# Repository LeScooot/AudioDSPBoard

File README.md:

## Members
Ryan Jeronimus, EE Student (Graduating 2027)

ryanjeronimus@vt.edu

## Mentor
MENTOR NAME HERE

## Current Status
IN PROGRESS

## Project Overview

PCB featuring 3.5mm audio inputs and outputs, an audio CODEC for high-quality audio sampling and reconstruction, bare-metal STM32 board for implementing DSP algorithms, and a small i2c LED display for displaying information pertaining to the audio effects implemented on the STM32 (real-time display). Features programmable potentiometers and buttons for use in DSP implementations. Battery powered for ease of use when travelling. The system is intended as a portable, real-time audio effects processor for general listening applications.

## Educational Value Added
This project teaches about PCB design, power electronics, bare-metal C programming practices, and DSP for audio applications (which includes topics widely applicable to general DSP). Audio-specific communication protocols such as i2s would also be taught with the completion of this project.
## Tasks

<!-- Your Text Here. You may work with your mentor on this later when they are assigned -->

## Design Decisions

<!-- Your Text Here. You may work with your mentor on this later when they are assigned -->

## Design Misc

<!-- Your Text Here. You may work with your mentor on this later when they are assigned -->

## Steps for Documenting Your Design Process

<!-- Your Text Here. You may work with your mentor on this later when they are assigned -->

## BOM + Component Cost

<!-- Your Text Here. You may work with your mentor on this later when they are assigned -->

## Timeline

<!-- Your Text Here. You may work with your mentor on this later when they are assigned -->

## Useful Links

<!-- Your Text Here. You may work with your mentor on this later when they are assigned -->

## Log

<!-- Your Text Here. You may work with your mentor on this later when they are assigned -->

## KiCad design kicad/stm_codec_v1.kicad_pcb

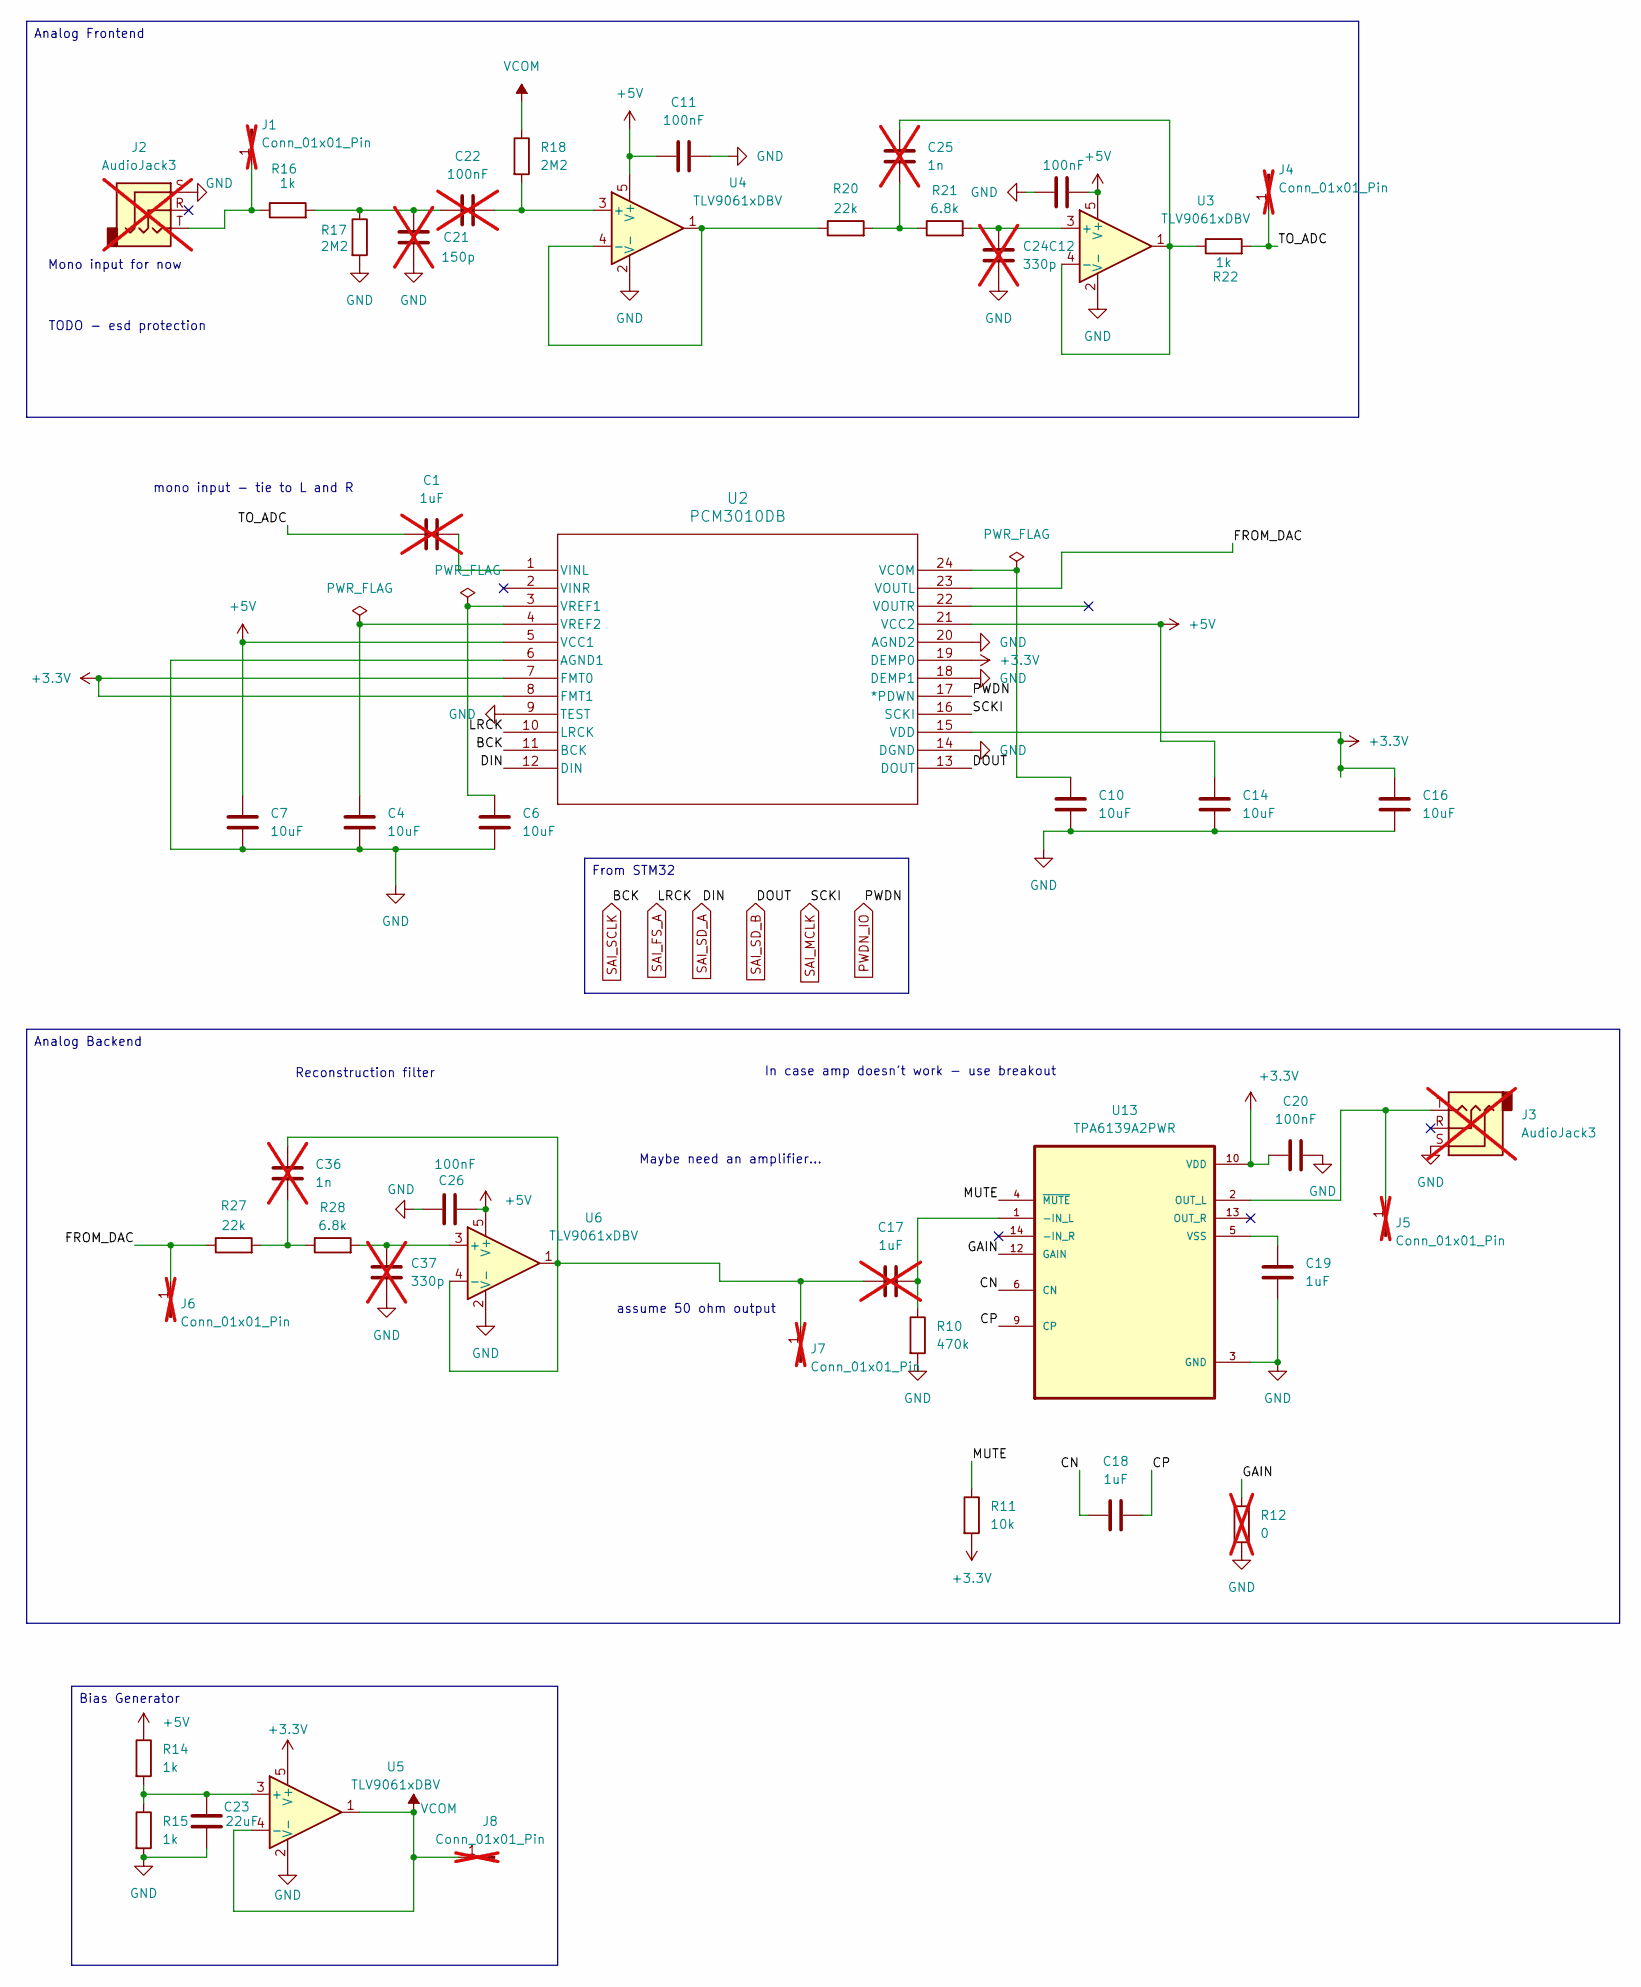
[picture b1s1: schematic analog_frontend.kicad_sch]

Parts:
C1, C17: 1uF; C_Rect_L16.5mm_W4.9mm_P15.00mm_MKT; not fitted
C4, C7: 10uF; C_0805_2012Metric_Pad1.18x1.45mm_HandSolder; LCSC Part # C15850
C6, C10, C14, C16: 10uF; C_1206_3216Metric_Pad1.33x1.80mm_HandSolder; LCSC Part # C13585
C11, C12, C20, C26: 100nF; C_0805_2012Metric_Pad1.18x1.45mm_HandSolder; LCSC Part # C49678
C18, C19: 1uF; C_1206_3216Metric_Pad1.33x1.80mm_HandSolder; LCSC Part # C1848
C21: 150p; C_Rect_L7.0mm_W2.5mm_P5.00mm; not fitted
C22: 100nF; C_Rect_L9.0mm_W4.0mm_P7.50mm_MKT; not fitted
C23: 22uF; C_1206_3216Metric_Pad1.33x1.80mm_HandSolder; LCSC Part # C12891
C24: 330p; C_Rect_L9.0mm_W4.0mm_P7.50mm_MKT; not fitted
C25, C36: 1n; C_Rect_L7.0mm_W2.5mm_P5.00mm; not fitted
C37: 330p; C_Rect_L7.0mm_W2.5mm_P5.00mm; not fitted
J1, J4, J5, J6, J7, J8: Conn_01x01_Pin; PinHeader_1x01_P2.54mm_Vertical; not fitted
J2, J3: AudioJack3; Jack_3.5mm_CUI_SJ-3523-SMT_Horizontal; not fitted
R10: 470k; R_0805_2012Metric_Pad1.20x1.40mm_HandSolder; LCSC Part # C17709
R11: 10k; R_0805_2012Metric_Pad1.20x1.40mm_HandSolder; LCSC Part # C17414
R12: 0; R_0805_2012Metric_Pad1.20x1.40mm_HandSolder; not fitted
R14, R15, R16, R22: 1k; R_0805_2012Metric_Pad1.20x1.40mm_HandSolder; LCSC Part # C702831
R17, R18: 2M2; R_0805_2012Metric_Pad1.20x1.40mm_HandSolder; LCSC Part # C17513
R20, R27: 22k; R_0805_2012Metric_Pad1.20x1.40mm_HandSolder; LCSC Part # C702833
R21, R28: 6.8k; R_0805_2012Metric_Pad1.20x1.40mm_HandSolder; LCSC Part # C17772
U2: PCM3010DB; DB24; LCSC Part # C2873586
U3, U4, U5, U6: TLV9061xDBV; SOT-23-5; LCSC Part # C398358
U13: TPA6139A2PWR; SOP65P640X120-14N; LCSC Part # C2870791

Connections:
+3.3V: C16.1, C20.1, R11.2, U2.7 (FMT0), U2.8 (FMT1), U2.15 (VDD), U2.19 (DEMP0), U5.5 (V+), U13.10 (VDD); also elsewhere on the board
+5V: C7.1, C11.1, C12.1, C14.1, C26.1, R14.1, U2.5 (VCC1), U2.21 (VCC2), U3.5 (V+), U4.5 (V+), U6.5 (V+); also elsewhere on the board
/Analog Frontend/CN: C18.1, U13.6 (CN)
/Analog Frontend/CP: C18.2, U13.9 (CP)
/Analog Frontend/FROM_DAC: J6.1, R27.1, U2.23 (VOUTL)
/Analog Frontend/GAIN: R12.1, U13.12 (GAIN)
/Analog Frontend/MUTE: R11.1, U13.4 (~MUTE)
/Analog Frontend/TO_ADC: C1.2, J4.1, R22.2
GND: C4.2, C6.2, C7.2, C10.2, C11.2, C12.2, C14.2, C16.2, C19.2, C20.2, C21.2, C23.2, C24.2, C26.2, C37.2, J2.S, J3.S, R10.2, R12.2, R15.2, R17.2, U2.6 (AGND1), U2.9 (TEST), U2.14 (DGND), U2.18 (DEMP1), U2.20 (AGND2), U3.2 (V-), U4.2 (V-), U5.2 (V-), U6.2 (V-), U13.3 (GND), U13.11 (GND); also elsewhere on the board
unnamed: C21.1, C22.2, R16.2, R17.1
unnamed: C25.2, R20.2, R21.1
unnamed: C36.2, R27.2, R28.1
unnamed: J1.1, J2.T, R16.1
unnamed: J3.T, J5.1, U13.2 (OUT_L)
unnamed: C17.1, C36.1, J7.1, U6.1, U6.4 (-)
unnamed: C10.1, U2.24 (VCOM)
unnamed: C1.1, U2.1 (VINL)
unnamed: C6.1, U2.3 (VREF1)
unnamed: C4.1, U2.4 (VREF2)
unnamed: C24.1, R21.2, U3.3 (+)
unnamed: C25.1, R22.1, U3.1, U3.4 (-)
unnamed: C22.1, R18.2, U4.3 (+)
unnamed: R20.1, U4.1, U4.4 (-)
unnamed: C23.1, R14.2, R15.1, U5.3 (+)
unnamed: C37.1, R28.2, U6.3 (+)
unnamed: C17.2, R10.1, U13.1 (-IN_L)
unnamed: C19.1, U13.5 (VSS)
PWDN_IO: U2.17 (*PDWN); also elsewhere on the board
SAI_FS_A: U2.10 (LRCK); also elsewhere on the board
SAI_MCLK: U2.16 (SCKI); also elsewhere on the board
SAI_SCLK: U2.11 (BCK); also elsewhere on the board
SAI_SD_A: U2.12 (DIN); also elsewhere on the board
SAI_SD_B: U2.13 (DOUT); also elsewhere on the board
VCOM: J8.1, R18.1, U5.1, U5.4 (-)

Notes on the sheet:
In case amp doesn't work - use breakout
assume 50 ohm output
Reconstruction filter
Maybe need an amplifier...
Mono input for now
mono input - tie to L and R
TODO - esd protection
Analog Frontend
Bias Generator
Analog Backend
From STM32

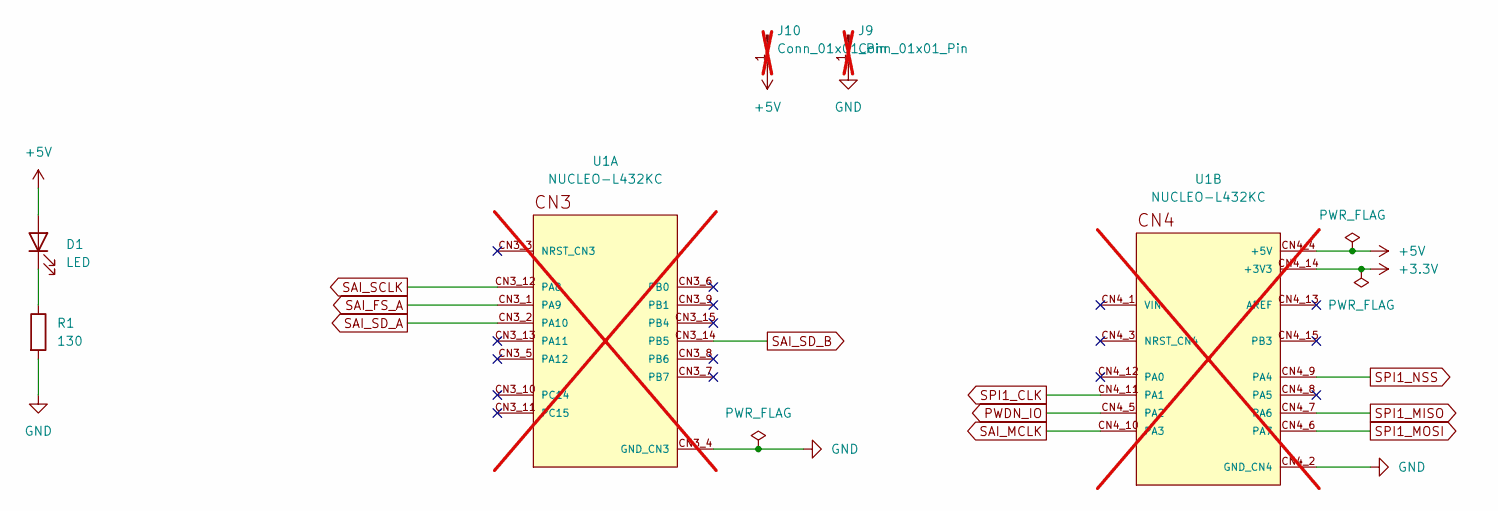
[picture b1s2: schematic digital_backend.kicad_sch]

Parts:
D1: LED; LED_0805_2012Metric_Pad1.15x1.40mm_HandSolder; LCSC Part # C2297
J9, J10: Conn_01x01_Pin; PinHeader_1x01_P2.54mm_Vertical; not fitted
R1: 130; R_0805_2012Metric_Pad1.20x1.40mm_HandSolder; LCSC Part # C178174
U1: NUCLEO-L432KC; MODULE_NUCLEO-L432KC; PARTREV N/A; not fitted

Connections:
+3.3V: U1.CN4_14 (+3V3); also elsewhere on the board
+5V: D1.2 (A), J10.1, U1.CN4_4 (+5V); also elsewhere on the board
GND: J9.1, R1.2, U1.CN3_4 (GND_CN3), U1.CN4_2 (GND_CN4); also elsewhere on the board
unnamed: D1.1 (K), R1.1
PWDN_IO: U1.CN4_5 (PA2); also elsewhere on the board
SAI_FS_A: U1.CN3_1 (PA9); also elsewhere on the board
SAI_MCLK: U1.CN4_10 (PA3); also elsewhere on the board
SAI_SCLK: U1.CN3_12 (PA8); also elsewhere on the board
SAI_SD_A: U1.CN3_2 (PA10); also elsewhere on the board
SAI_SD_B: U1.CN3_14 (PB5); also elsewhere on the board
SPI1_CLK: U1.CN4_11 (PA1)
SPI1_MISO: U1.CN4_7 (PA6)
SPI1_MOSI: U1.CN4_6 (PA7)
SPI1_NSS: U1.CN4_9 (PA4)

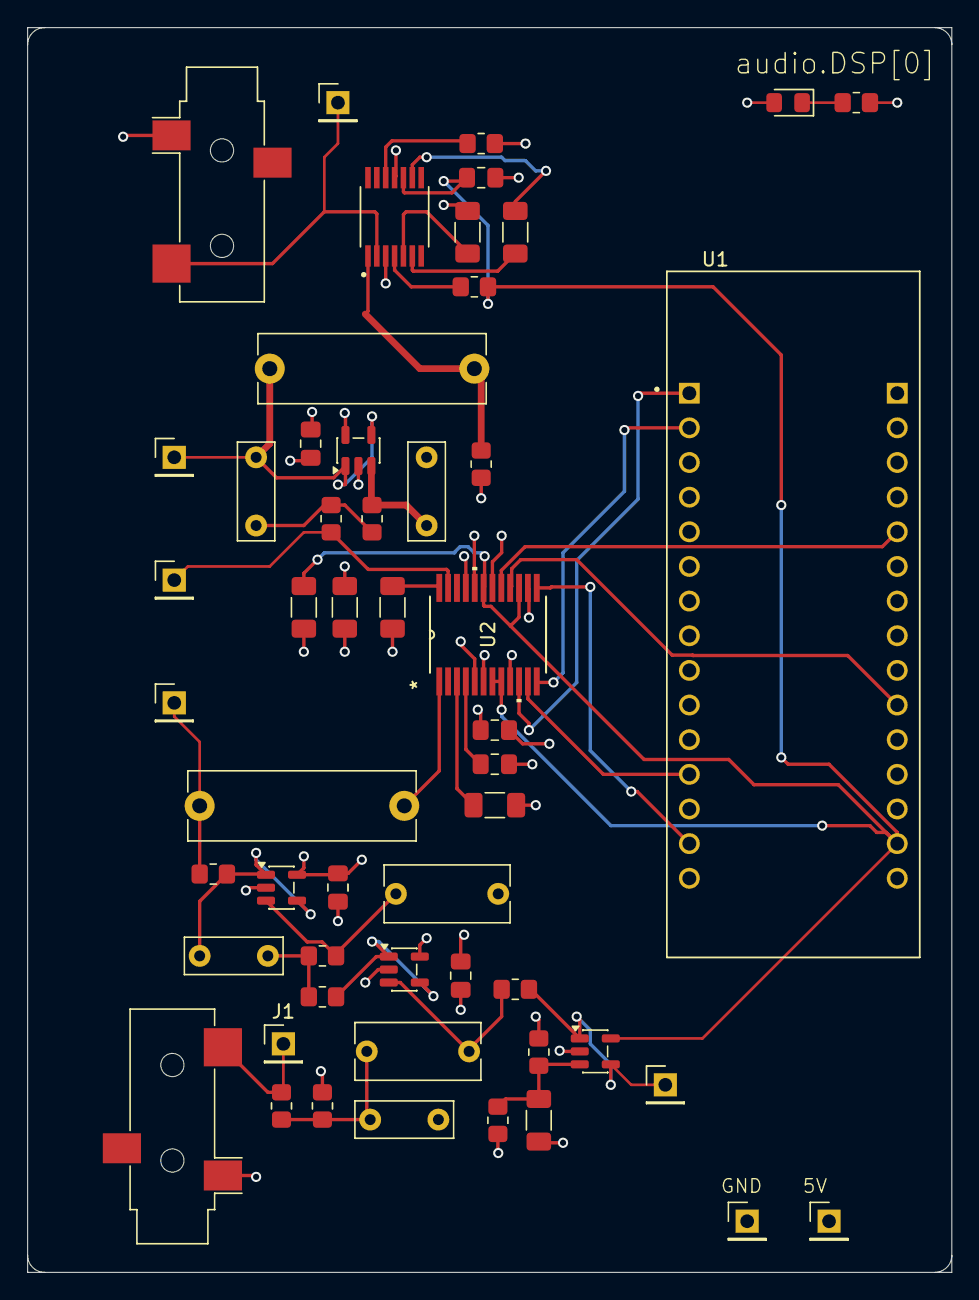
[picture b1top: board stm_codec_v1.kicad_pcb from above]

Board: 4 copper layers, 67.8 x 91.2 mm, 53 parts (0 on the bottom side), 35 nets.

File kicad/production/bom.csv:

Designator,Footprint,Quantity,Value,LCSC Part #
"C10, C14, C16, C6",1206,4,10uF,C13585
"C11, C12, C20, C26",0805,4,100nF,C49678
"C18, C19",1206,2,1uF,C1848
C23,1206,1,22uF,C12891
"C4, C7",0805,2,10uF,C15850
D1,0805,1,LED,C2297
R1,0805,1,130,C178174
R10,0805,1,470k,C17709
R11,0805,1,10k,C17414
"R14, R15, R16, R22",0805,4,1k,C702831
"R17, R18",0805,2,2M2,C17513
"R20, R27",0805,2,22k,C702833
"R21, R28",0805,2,6.8k,C17772
U13,SOP65P640X120-14N,1,TPA6139A2PWR,C2870791
U2,DB24,1,PCM3010DB,C2873586
"U3, U4, U5, U6",SOT-23-5,4,TLV9061xDBV,C398358

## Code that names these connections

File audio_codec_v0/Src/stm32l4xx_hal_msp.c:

/* USER CODE BEGIN Header */
/**
  ******************************************************************************
  * @file         stm32l4xx_hal_msp.c
  * @brief        This file provides code for the MSP Initialization
  *               and de-Initialization codes.
  ******************************************************************************
  * @attention
  *
  * Copyright (c) 2026 STMicroelectronics.
  * All rights reserved.
  *
  * This software is licensed under terms that can be found in the LICENSE file
  * in the root directory of this software component.
  * If no LICENSE file comes with this software, it is provided AS-IS.
  *
  ******************************************************************************
  */
/* USER CODE END Header */
/* Includes ------------------------------------------------------------------*/
#include "main.h"
/* USER CODE BEGIN Includes */

/* USER CODE END Includes */

/* Private typedef -----------------------------------------------------------*/
/* USER CODE BEGIN TD */

/* USER CODE END TD */

/* Private define ------------------------------------------------------------*/
/* USER CODE BEGIN Define */

/* USER CODE END Define */

/* Private macro -------------------------------------------------------------*/
/* USER CODE BEGIN Macro */

/* USER CODE END Macro */

/* Private variables ---------------------------------------------------------*/
/* USER CODE BEGIN PV */

/* USER CODE END PV */

/* Private function prototypes -----------------------------------------------*/
/* USER CODE BEGIN PFP */

/* USER CODE END PFP */

/* External functions --------------------------------------------------------*/
/* USER CODE BEGIN ExternalFunctions */

/* USER CODE END ExternalFunctions */

/* USER CODE BEGIN 0 */

/* USER CODE END 0 */
/**
  * Initializes the Global MSP.
  */
void HAL_MspInit(void)
{

  /* USER CODE BEGIN MspInit 0 */

  /* USER CODE END MspInit 0 */

  __HAL_RCC_SYSCFG_CLK_ENABLE();
  __HAL_RCC_PWR_CLK_ENABLE();

  /* System interrupt init*/

  /* USER CODE BEGIN MspInit 1 */

  /* USER CODE END MspInit 1 */
}

/**
  * @brief UART MSP Initialization
  * This function configures the hardware resources used in this example
  * @param huart: UART handle pointer
  * @retval None
  */
void HAL_UART_MspInit(UART_HandleTypeDef* huart)
{
  GPIO_InitTypeDef GPIO_InitStruct = {0};
  RCC_PeriphCLKInitTypeDef PeriphClkInit = {0};
  if(huart->Instance==USART2)
  {
    /* USER CODE BEGIN USART2_MspInit 0 */

    /* USER CODE END USART2_MspInit 0 */

  /** Initializes the peripherals clock
  */
    PeriphClkInit.PeriphClockSelection = RCC_PERIPHCLK_USART2;
    PeriphClkInit.Usart2ClockSelection = RCC_USART2CLKSOURCE_PCLK1;
    if (HAL_RCCEx_PeriphCLKConfig(&PeriphClkInit) != HAL_OK)
    {
      Error_Handler();
    }

    /* Peripheral clock enable */
    __HAL_RCC_USART2_CLK_ENABLE();

    __HAL_RCC_GPIOA_CLK_ENABLE();
    /**USART2 GPIO Configuration
    PA2     ------> USART2_TX
    PA15 (JTDI)     ------> USART2_RX
    */
    GPIO_InitStruct.Pin = VCP_TX_Pin;
    GPIO_InitStruct.Mode = GPIO_MODE_AF_PP;
    GPIO_InitStruct.Pull = GPIO_NOPULL;
    GPIO_InitStruct.Speed = GPIO_SPEED_FREQ_VERY_HIGH;
    GPIO_InitStruct.Alternate = GPIO_AF7_USART2;
    HAL_GPIO_Init(VCP_TX_GPIO_Port, &GPIO_InitStruct);

    GPIO_InitStruct.Pin = VCP_RX_Pin;
    GPIO_InitStruct.Mode = GPIO_MODE_AF_PP;
    GPIO_InitStruct.Pull = GPIO_NOPULL;
    GPIO_InitStruct.Speed = GPIO_SPEED_FREQ_VERY_HIGH;
    GPIO_InitStruct.Alternate = GPIO_AF3_USART2;
    HAL_GPIO_Init(VCP_RX_GPIO_Port, &GPIO_InitStruct);

    /* USER CODE BEGIN USART2_MspInit 1 */

    /* USER CODE END USART2_MspInit 1 */

  }

}

/**
  * @brief UART MSP De-Initialization
  * This function freeze the hardware resources used in this example
  * @param huart: UART handle pointer
  * @retval None
  */
void HAL_UART_MspDeInit(UART_HandleTypeDef* huart)
{
  if(huart->Instance==USART2)
  {
    /* USER CODE BEGIN USART2_MspDeInit 0 */

    /* USER CODE END USART2_MspDeInit 0 */
    /* Peripheral clock disable */
    __HAL_RCC_USART2_CLK_DISABLE();

    /**USART2 GPIO Configuration
    PA2     ------> USART2_TX
    PA15 (JTDI)     ------> USART2_RX
    */
    HAL_GPIO_DeInit(GPIOA, VCP_TX_Pin|VCP_RX_Pin);

    /* USER CODE BEGIN USART2_MspDeInit 1 */

    /* USER CODE END USART2_MspDeInit 1 */
  }

}

extern DMA_HandleTypeDef hdma_sai1_a;

extern DMA_HandleTypeDef hdma_sai1_b;

static uint32_t SAI1_client =0;

void HAL_SAI_MspInit(SAI_HandleTypeDef* hsai)
{

  GPIO_InitTypeDef GPIO_InitStruct;
/* SAI1 */
    if(hsai->Instance==SAI1_Block_A)
    {
    /* Peripheral clock enable */
    if (SAI1_client == 0)
    {
       __HAL_RCC_SAI1_CLK_ENABLE();
    }
    SAI1_client ++;

    /**SAI1_A_Block_A GPIO Configuration
    PA3     ------> SAI1_MCLK_A
    PA8     ------> SAI1_SCK_A
    PA9     ------> SAI1_FS_A
    PA10     ------> SAI1_SD_A
    */
    GPIO_InitStruct.Pin = GPIO_PIN_3|GPIO_PIN_8|GPIO_PIN_9|GPIO_PIN_10;
    GPIO_InitStruct.Mode = GPIO_MODE_AF_PP;
    GPIO_InitStruct.Pull = GPIO_NOPULL;
    GPIO_InitStruct.Speed = GPIO_SPEED_FREQ_LOW;
    GPIO_InitStruct.Alternate = GPIO_AF13_SAI1;
    HAL_GPIO_Init(GPIOA, &GPIO_InitStruct);

      /* Peripheral DMA init*/

    hdma_sai1_a.Instance = DMA2_Channel1;
    hdma_sai1_a.Init.Request = DMA_REQUEST_1;
    hdma_sai1_a.Init.Direction = DMA_MEMORY_TO_PERIPH;
    hdma_sai1_a.Init.PeriphInc = DMA_PINC_DISABLE;
    hdma_sai1_a.Init.MemInc = DMA_MINC_ENABLE;
    hdma_sai1_a.Init.PeriphDataAlignment = DMA_PDATAALIGN_WORD;
    hdma_sai1_a.Init.MemDataAlignment = DMA_MDATAALIGN_WORD;
    hdma_sai1_a.Init.Mode = DMA_CIRCULAR;
    hdma_sai1_a.Init.Priority = DMA_PRIORITY_VERY_HIGH;
    if (HAL_DMA_Init(&hdma_sai1_a) != HAL_OK)
    {
      Error_Handler();
    }

    /* Several peripheral DMA handle pointers point to the same DMA handle.
     Be aware that there is only one channel to perform all the requested DMAs. */
    __HAL_LINKDMA(hsai,hdmarx,hdma_sai1_a);

    __HAL_LINKDMA(hsai,hdmatx,hdma_sai1_a);

    }
    if(hsai->Instance==SAI1_Block_B)
    {
      /* Peripheral clock enable */
      if (SAI1_client == 0)
      {
       __HAL_RCC_SAI1_CLK_ENABLE();
      }
    SAI1_client ++;

    /**SAI1_B_Block_B GPIO Configuration
    PB5     ------> SAI1_SD_B
    */
    GPIO_InitStruct.Pin = GPIO_PIN_5;
    GPIO_InitStruct.Mode = GPIO_MODE_AF_PP;
    GPIO_InitStruct.Pull = GPIO_NOPULL;
    GPIO_InitStruct.Speed = GPIO_SPEED_FREQ_LOW;
    GPIO_InitStruct.Alternate = GPIO_AF13_SAI1;
    HAL_GPIO_Init(GPIOB, &GPIO_InitStruct);

      /* Peripheral DMA init*/

    hdma_sai1_b.Instance = DMA2_Channel2;
    hdma_sai1_b.Init.Request = DMA_REQUEST_1;
    hdma_sai1_b.Init.Direction = DMA_PERIPH_TO_MEMORY;
    hdma_sai1_b.Init.PeriphInc = DMA_PINC_DISABLE;
    hdma_sai1_b.Init.MemInc = DMA_MINC_ENABLE;
    hdma_sai1_b.Init.PeriphDataAlignment = DMA_PDATAALIGN_WORD;
    hdma_sai1_b.Init.MemDataAlignment = DMA_MDATAALIGN_WORD;
    hdma_sai1_b.Init.Mode = DMA_CIRCULAR;
    hdma_sai1_b.Init.Priority = DMA_PRIORITY_VERY_HIGH;
    if (HAL_DMA_Init(&hdma_sai1_b) != HAL_OK)
    {
      Error_Handler();
    }

    /* Several peripheral DMA handle pointers point to the same DMA handle.
     Be aware that there is only one channel to perform all the requested DMAs. */
    __HAL_LINKDMA(hsai,hdmarx,hdma_sai1_b);
    __HAL_LINKDMA(hsai,hdmatx,hdma_sai1_b);
    }
}

void HAL_SAI_MspDeInit(SAI_HandleTypeDef* hsai)
{
/* SAI1 */
    if(hsai->Instance==SAI1_Block_A)
    {
    SAI1_client --;
    if (SAI1_client == 0)
      {
      /* Peripheral clock disable */
       __HAL_RCC_SAI1_CLK_DISABLE();
      }

    /**SAI1_A_Block_A GPIO Configuration
    PA3     ------> SAI1_MCLK_A
    PA8     ------> SAI1_SCK_A
    PA9     ------> SAI1_FS_A
    PA10     ------> SAI1_SD_A
    */
    HAL_GPIO_DeInit(GPIOA, GPIO_PIN_3|GPIO_PIN_8|GPIO_PIN_9|GPIO_PIN_10);

    /* SAI1 DMA Deinit */
    HAL_DMA_DeInit(hsai->hdmarx);
    HAL_DMA_DeInit(hsai->hdmatx);
    }
    if(hsai->Instance==SAI1_Block_B)
    {
    SAI1_client --;
      if (SAI1_client == 0)
      {
      /* Peripheral clock disable */
      __HAL_RCC_SAI1_CLK_DISABLE();
      }

    /**SAI1_B_Block_B GPIO Configuration
    PB5     ------> SAI1_SD_B
    */
    HAL_GPIO_DeInit(GPIOB, GPIO_PIN_5);

    /* SAI1 DMA Deinit */
    HAL_DMA_DeInit(hsai->hdmarx);
    HAL_DMA_DeInit(hsai->hdmatx);
    }
}

/* USER CODE BEGIN 1 */

/* USER CODE END 1 */

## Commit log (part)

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2026-02-18 schematic finished
